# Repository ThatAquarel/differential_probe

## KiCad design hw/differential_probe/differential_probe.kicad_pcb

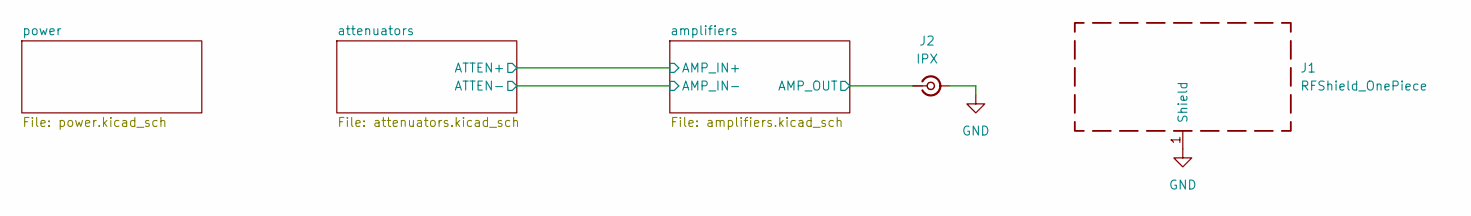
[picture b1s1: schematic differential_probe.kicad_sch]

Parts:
J1: RFShield_OnePiece
J2: IPX; BWIPX-1-001E; MFR PART # C496552

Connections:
/amplifiers/AMP_OUT: J2.1 (In); also elsewhere on the board
GND: J1.1, J2.2 (Ext); also elsewhere on the board

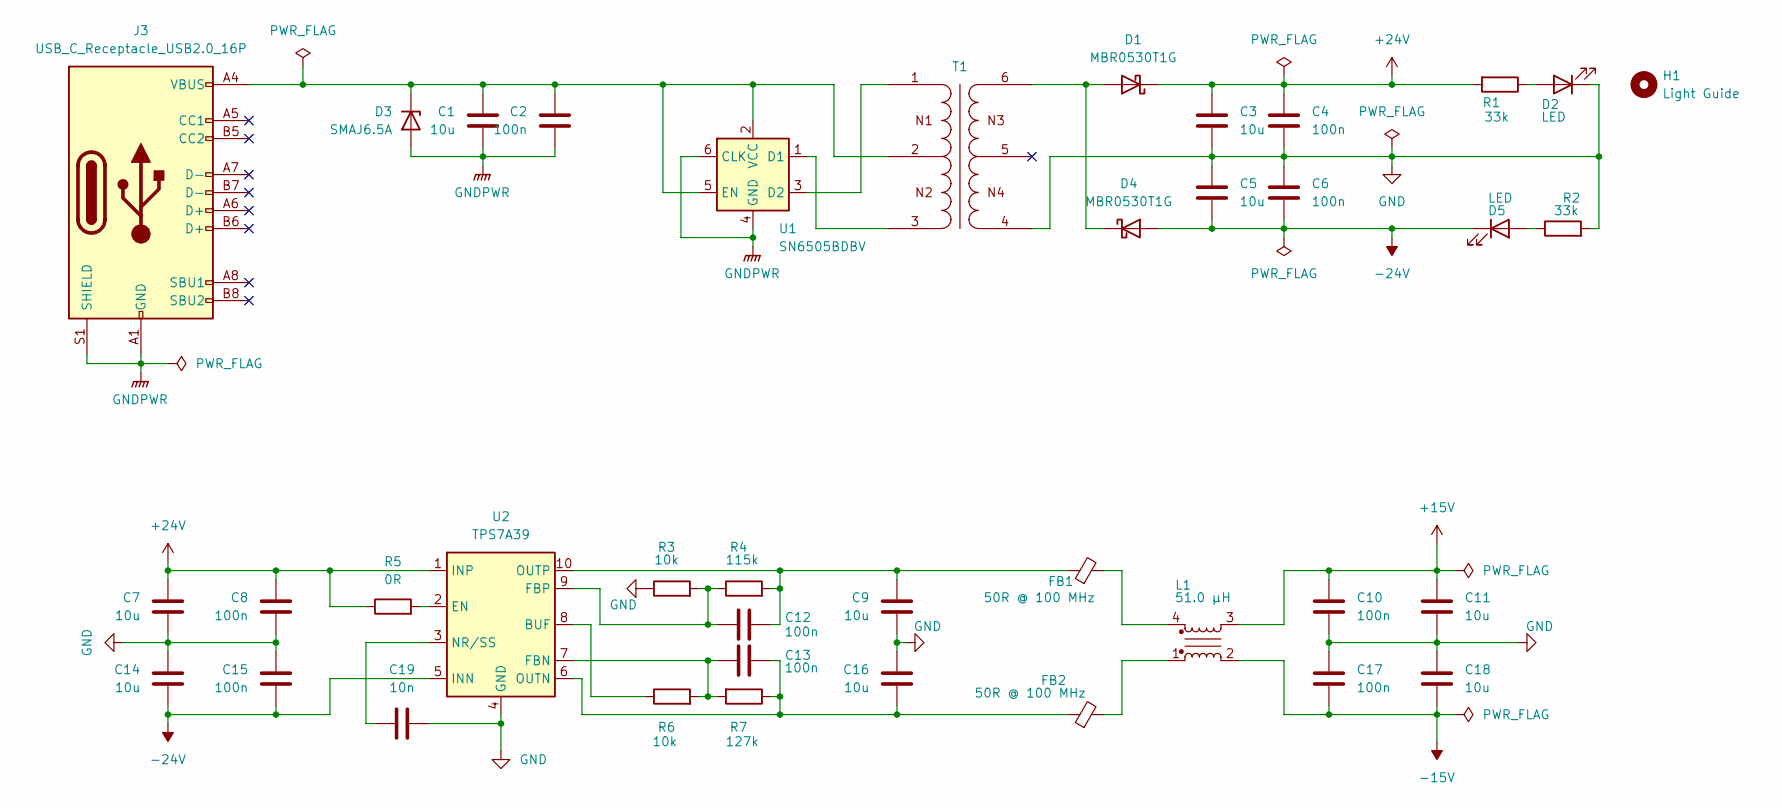
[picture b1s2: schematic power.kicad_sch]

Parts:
C1, C3, C5, C7, C9, C11, C14, C16, C18: 10u; C_1206_3216Metric; LCSC C13585
C2, C4, C6, C8, C10, C12, C13, C15, C17: 100n; C_0402_1005Metric; LCSC C307331
C19: 10n; C_0805_2012Metric; LCSC C1710
D1, D4: MBR0530T1G; D_SOD-123; MFR PART # MBR0530T1G
D2, D5: LED; LED_0805_2012Metric; LCSC C34499
D3: SMAJ6.5A; D_SMA_Handsoldering; MFR PART # SMAJ6.5A
FB1, FB2: 50R @ 100 MHz; L_0402_1005Metric_Pad0.77x0.64mm_HandSolder; MFR PART # LQW15AN47NJ00D
H1: Light Guide; SLP3-150-100-F
J3: USB_C_Receptacle_USB2.0_16P; USB_C_Receptacle_G-Switch_GT-USB-7043; LCSC C2762982
L1: 1812_744235510; L_Wurth_WE-CNSW-1812; Part Number 744235510
R1, R2: 33k; R_0805_2012Metric; LCSC C17633
R3, R6: 10k; R_0402_1005Metric; LCSC C25744
R4: 115k; R_0402_1005Metric_Pad0.72x0.64mm_HandSolder; MFR PART # ERJ-2RKF1153X
R5: 0R; R_0402_1005Metric_Pad0.72x0.64mm_HandSolder; LCSC C17168
R7: 127k; R_0402_1005Metric_Pad0.72x0.64mm_HandSolder; MFR PART # ERJ-2RKF1273X
T1: 1006_760390014; T_Wurth_WE-PPTI-1006; Part Number 760390014
U1: SN6505BDBV; SOT-23-6; LCSC C74518
U2: TPS7A39; Texas_S-PVSON-N10_ThermalVias; LCSC C2685819

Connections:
+15V: C10.1, C11.1, L1.3; also elsewhere on the board
+24V: C3.1, C4.1, C7.1, C8.1, D1.1 (K), R1.2, R5.1, U2.1 (INP)
-15V: C17.2, C18.2, L1.2; also elsewhere on the board
-24V: C5.2, C6.2, C14.2, C15.2, D4.2 (A), D5.1 (K), U2.5 (INN)
GND: C3.2, C4.2, C5.1, C6.1, C7.2, C8.2, C9.2, C10.2, C11.2, C14.1, C15.1, C16.1, C17.1, C18.1, C19.2, D2.1 (K), R2.2, R3.1, T1.4, U2.4 (GND), U2.11 (GND); also elsewhere on the board
GNDPWR: C1.2, C2.2, D3.2 (A), J3.A1 (GND), J3.A12 (GND), J3.B1 (GND), J3.B12 (GND), J3.S1 (SHIELD), U1.4 (GND), U1.6 (CLK)
unnamed: D1.2 (A), D4.1 (K), T1.6
unnamed: D2.2 (A), R1.1
unnamed: C1.1, C2.1, D3.1 (K), J3.A4 (VBUS), J3.A9 (VBUS), J3.B4 (VBUS), J3.B9 (VBUS), T1.2, U1.2 (VCC), U1.5 (EN)
unnamed: D5.2 (A), R2.1
unnamed: FB1.2, L1.4
unnamed: FB2.2, L1.1
unnamed: T1.3, U1.1 (D1)
unnamed: T1.1, U1.3 (D2)
unnamed: R6.1, U2.8 (BUF)
unnamed: R5.2, U2.2 (EN)
unnamed: C13.2, R6.2, R7.2, U2.7 (FBN)
unnamed: C12.2, R3.2, R4.1, U2.9 (FBP)
unnamed: C19.1, U2.3 (NR/SS)
unnamed: C13.1, C16.2, FB2.1, R7.1, U2.6 (OUTN)
unnamed: C9.1, C12.1, FB1.1, R4.2, U2.10 (OUTP)

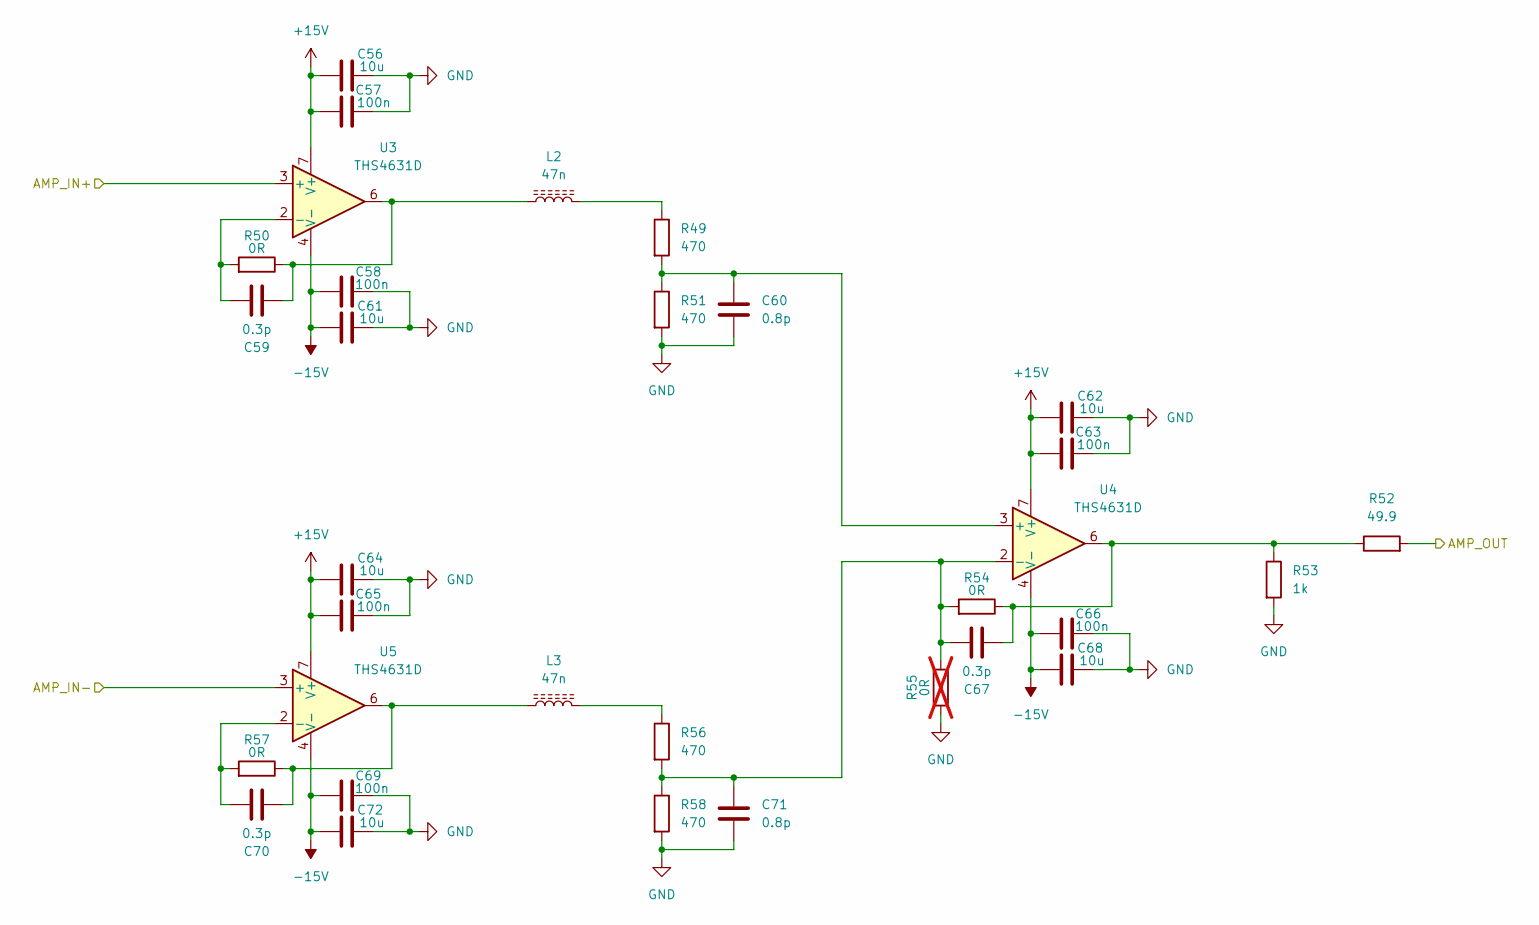
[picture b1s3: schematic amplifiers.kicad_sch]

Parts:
C56, C61, C62, C64, C68, C72: 10u; C_1206_3216Metric; LCSC C13585
C57, C58, C63, C65, C66, C69: 100n; C_0402_1005Metric; LCSC C307331
C59, C67, C70: 0.3p; C_0402_1005Metric_Pad0.74x0.62mm_HandSolder; MFR PART # GJM1555C1HR30WB01D
C60, C71: 0.8p; C_0402_1005Metric_Pad0.74x0.62mm_HandSolder; MFR PART # GJM1555C1HR80WB01D
L2, L3: 47n; L_0402_1005Metric_Pad0.77x0.64mm_HandSolder; MFR PART # LQW15AN47NJ00D
R49, R51, R56, R58: 470; R_0805_2012Metric; LCSC C17710
R50, R54, R57: 0R; R_0402_1005Metric_Pad0.72x0.64mm_HandSolder; LCSC C17168
R52: 49.9; R_0805_2012Metric; LCSC C17720
R53: 1k; R_1206_3216Metric; LCSC C4410
R55: 0R; R_0402_1005Metric_Pad0.72x0.64mm_HandSolder; not fitted
U3, U4, U5: THS4631D; SOIC-8_3.9x4.9mm_P1.27mm; MFR PART # THS4631DR

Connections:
+15V: C56.1, C57.2, C62.1, C63.2, C64.1, C65.2, U3.7 (V+), U4.7 (V+), U5.7 (V+); also elsewhere on the board
-15V: C58.1, C61.1, C66.1, C68.1, C69.1, C72.1, U3.4 (V-), U4.4 (V-), U5.4 (V-); also elsewhere on the board
/amplifiers/AMP_IN+: U3.3 (+); also elsewhere on the board
/amplifiers/AMP_IN-: U5.3 (+); also elsewhere on the board
/amplifiers/AMP_OUT: R52.2; also elsewhere on the board
GND: C56.2, C57.1, C58.2, C60.2, C61.2, C62.2, C63.1, C64.2, C65.1, C66.2, C68.2, C69.2, C71.2, C72.2, R51.2, R53.2, R55.2, R58.2; also elsewhere on the board
unnamed: C59.2, L2.1, R50.1, U3.6
unnamed: C67.2, R52.1, R53.1, R54.1, U4.6
unnamed: C70.2, L3.1, R57.1, U5.6
unnamed: L2.2, R49.1
unnamed: L3.2, R56.1
unnamed: C59.1, R50.2, U3.2 (-)
unnamed: C60.1, R49.2, R51.1, U4.3 (+)
unnamed: C67.1, C71.1, R54.2, R55.1, R56.2, R58.1, U4.2 (-)
unnamed: C70.1, R57.2, U5.2 (-)

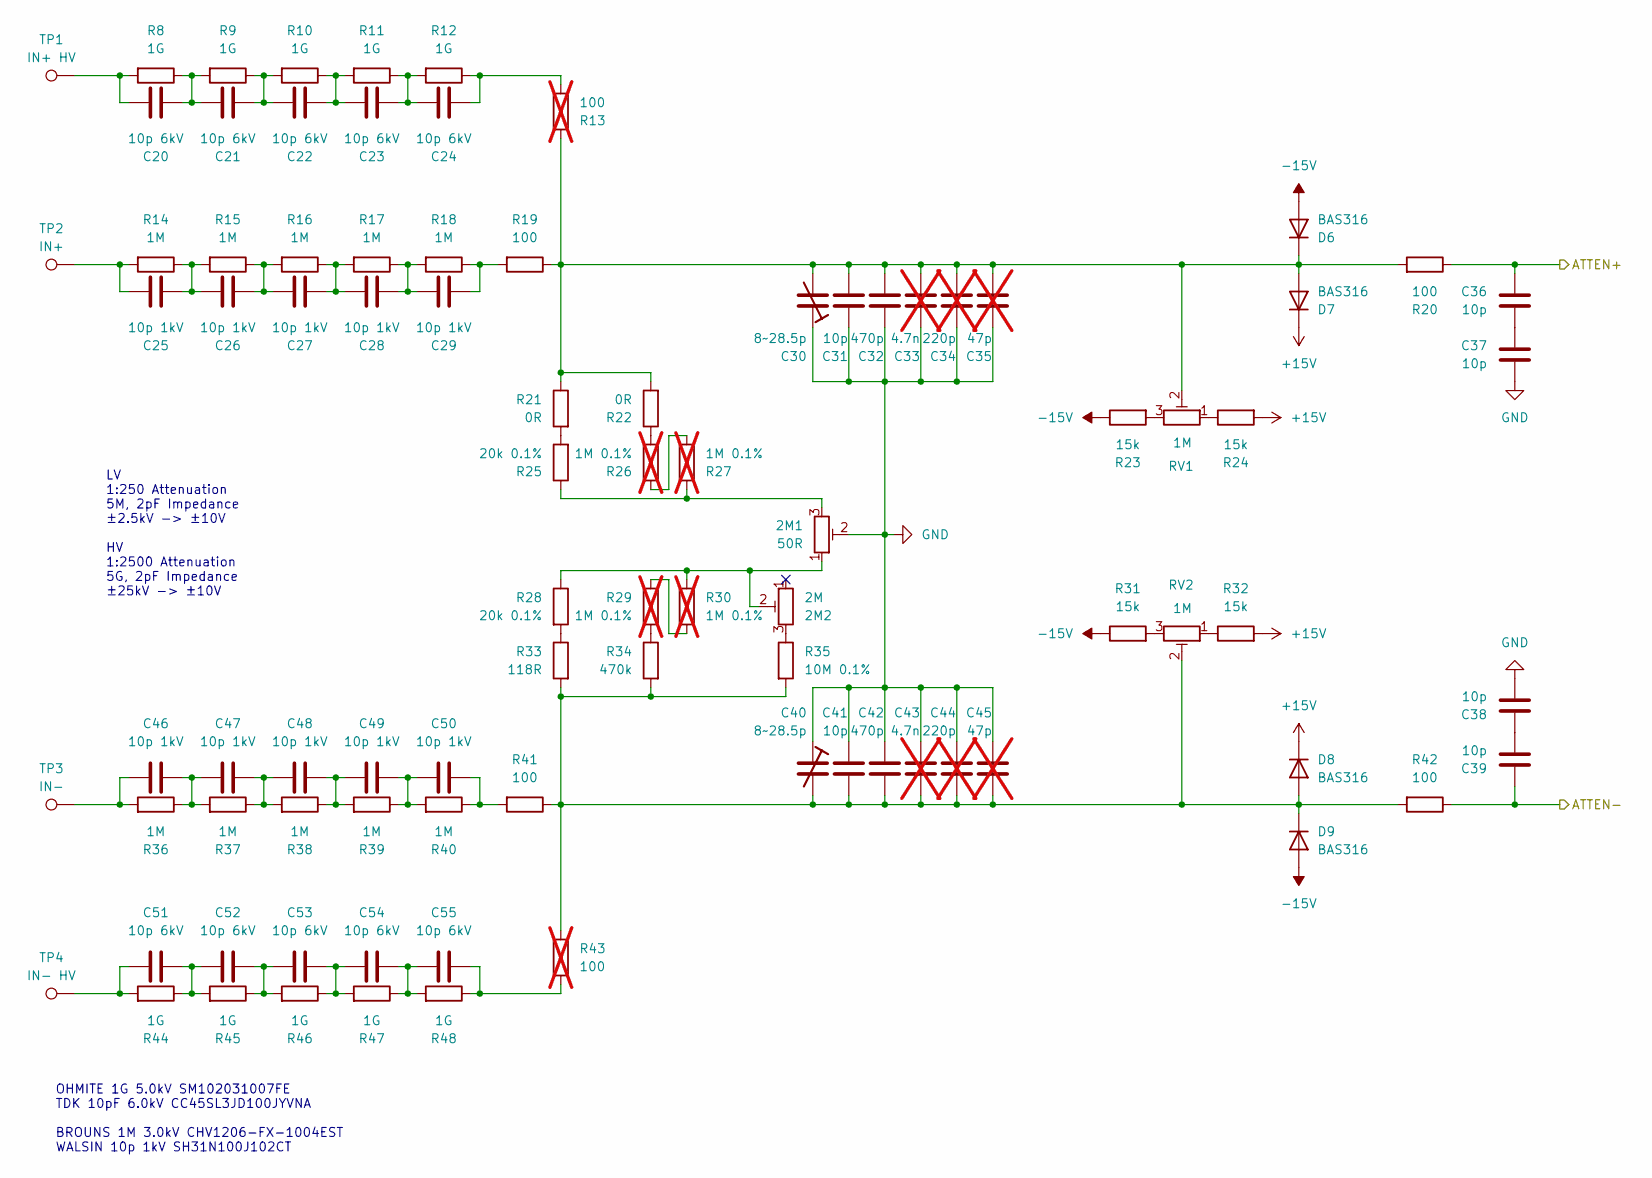
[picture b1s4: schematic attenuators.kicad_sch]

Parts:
2M1: 50R; Potentiometer_Bourns_3296W_Vertical; MFR PART # 3296W-1-500LF
2M2: 2M; Potentiometer_Bourns_3296W_Vertical; MFR PART # 3296W-1-205LF
C20, C21, C22, C23, C24, C51, C52, C53, C54, C55: 10p 6kV; C_Rect_L9.0mm_W6.4mm_P7.50mm_MKT; MFR PART # CC45SL3JD100JYVNA
C25, C26, C27, C28, C29, C46, C47, C48, C49, C50: 10p 1kV; C_1206_3216Metric_Pad1.33x1.80mm_HandSolder; MFR PART # SH31N100J102CT
C30, C40: 8~28.5p; C_Trimmer_Voltronics_JZ; LCSC C22468123
C31, C36, C37, C38, C39, C41: 10p; C_0805_2012Metric; LCSC C1743
C32, C42: 470p; C_0805_2012Metric; LCSC C1743
C33, C43: 4.7n; C_0805_2012Metric_Pad1.18x1.45mm_HandSolder; MFR PART # C0805C472J2GEC7210; not fitted
C34, C44: 220p; C_0805_2012Metric_Pad1.18x1.45mm_HandSolder; MFR PART # CC0805JRNPO9BN221; not fitted
C35, C45: 47p; C_0805_2012Metric_Pad1.18x1.45mm_HandSolder; MFR PART # C0805X470J5GACTU; not fitted
D6, D7, D8, D9: BAS316; D_SOD-323; MFR PART # BAS316
R8, R9, R10, R11, R12, R44, R45, R46, R47, R48: 1G; R_Axial_DIN0207_L6.3mm_D2.5mm_P10.16mm_Horizontal; MFR PART # SM102031007FE
R13, R43: 100; R_0805_2012Metric; not fitted
R14, R15, R16, R17, R18, R36, R37, R38, R39, R40: 1M; R_1206_3216Metric_Pad1.30x1.75mm_HandSolder; MFR PART # CHV1206-FX-1004EST
R19, R20, R41, R42: 100; R_1206_3216Metric_Pad1.30x1.75mm_HandSolder; LCSC C17901
R21, R22: 0R; R_1206_3216Metric_Pad1.30x1.75mm_HandSolder; LCSC C17888
R23, R24, R31, R32: 15k; R_0603_1608Metric; LCSC C22809
R25, R28: 20k 0.1%; R_1206_3216Metric_Pad1.30x1.75mm_HandSolder; MFR PART # RNCF1206BTE20K0
R26, R27, R29, R30: 1M 0.1%; R_1206_3216Metric_Pad1.30x1.75mm_HandSolder; MFR PART # RNCS1206BKE1M00; not fitted
R33: 118R; R_1206_3216Metric_Pad1.30x1.75mm_HandSolder; MFR PART # RMCF1206FT118R
R34: 470k; R_0805_2012Metric; MFR PART # C17709
R35: 10M 0.1%; R_1206_3216Metric_Pad1.30x1.75mm_HandSolder; MFR PART # MCA1206MD1005BP100
RV1, RV2: 1M; Potentiometer_Bourns_3296Y_Vertical; MFR PART # 3296Y-1-105LF
TP1: IN+ HV; TestPoint_Loop_D2.50mm_Drill1.85mm
TP2: IN+; TestPoint_Loop_D2.50mm_Drill1.85mm
TP3: IN-; TestPoint_Loop_D2.50mm_Drill1.85mm
TP4: IN- HV; TestPoint_Loop_D2.50mm_Drill1.85mm

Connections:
+15V: D7.1 (K), D8.1 (K), R24.2, R32.2; also elsewhere on the board
-15V: D6.2 (A), D9.2 (A), R23.1, R31.1; also elsewhere on the board
/amplifiers/AMP_IN+: C36.1, R20.1; also elsewhere on the board
/amplifiers/AMP_IN-: C39.1, R42.1; also elsewhere on the board
GND: 2M1.2, C30.1, C31.1, C32.1, C33.1, C34.1, C35.1, C37.2, C38.2, C40.1, C41.1, C42.1, C43.1, C44.1, C45.1; also elsewhere on the board
unnamed: 2M1.1, 2M2.2, R28.1, R30.1
unnamed: 2M1.3, R25.1, R27.1
unnamed: 2M2.3, R35.1
unnamed: C20.1, R8.2, TP1.1
unnamed: C20.2, C21.1, R8.1, R9.2
unnamed: C21.2, C22.1, R9.1, R10.2
unnamed: C22.2, C23.1, R10.1, R11.2
unnamed: C23.2, C24.1, R11.1, R12.2
unnamed: C24.2, R12.1, R13.1
unnamed: C25.1, R14.2, TP2.1
unnamed: C25.2, C26.1, R14.1, R15.2
unnamed: C26.2, C27.1, R15.1, R16.2
unnamed: C27.2, C28.1, R16.1, R17.2
unnamed: C28.2, C29.1, R17.1, R18.2
unnamed: C29.2, R18.1, R19.2
unnamed: C36.2, C37.1
unnamed: C38.1, C39.2
unnamed: C46.1, R36.2, TP3.1
unnamed: C46.2, C47.1, R36.1, R37.2
unnamed: C47.2, C48.1, R37.1, R38.2
unnamed: C48.2, C49.1, R38.1, R39.2
unnamed: C49.2, C50.1, R39.1, R40.2
unnamed: C50.2, R40.1, R41.2
unnamed: C51.1, R44.2, TP4.1
unnamed: C51.2, C52.1, R44.1, R45.2
unnamed: C52.2, C53.1, R45.1, R46.2
unnamed: C53.2, C54.1, R46.1, R47.2
unnamed: C54.2, C55.1, R47.1, R48.2
unnamed: C55.2, R43.1, R48.1
unnamed: C30.2, C31.2, C32.2, C33.2, C34.2, C35.2, D6.1 (K), D7.2 (A), R13.2, R19.1, R20.2, R21.1, R22.2, RV1.2
unnamed: C40.2, C41.2, C42.2, C43.2, C44.2, C45.2, D8.2 (A), D9.1 (K), R33.2, R34.2, R35.2, R41.1, R42.2, R43.2, RV2.2
unnamed: R21.2, R25.2
unnamed: R22.1, R26.2
unnamed: R23.2, RV1.3
unnamed: R24.1, RV1.1
unnamed: R26.1, R27.2
unnamed: R28.2, R33.1
unnamed: R29.1, R30.2
unnamed: R29.2, R34.1
unnamed: R31.2, RV2.3
unnamed: R32.1, RV2.1

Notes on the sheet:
OHMITE 1G 5.0kV SM102031007FE TDK 10pF 6.0kV CC45SL3JD100JYVNA BROUNS 1M 3.0kV CHV1206-FX-1004EST WALSIN 10p 1kV SH31N100J102CT
LV 1:250 Attenuation 5M, 2pF Impedance ±2.5kV -> ±10V HV 1:2500 Attenuation 5G, 2pF Impedance ±25kV -> ±10V

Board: 2 copper layers, 161 parts (0 on the bottom side), 74 nets, no tracks yet.

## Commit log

2026-02-07 initial schematic
2026-02-07 initial routing
